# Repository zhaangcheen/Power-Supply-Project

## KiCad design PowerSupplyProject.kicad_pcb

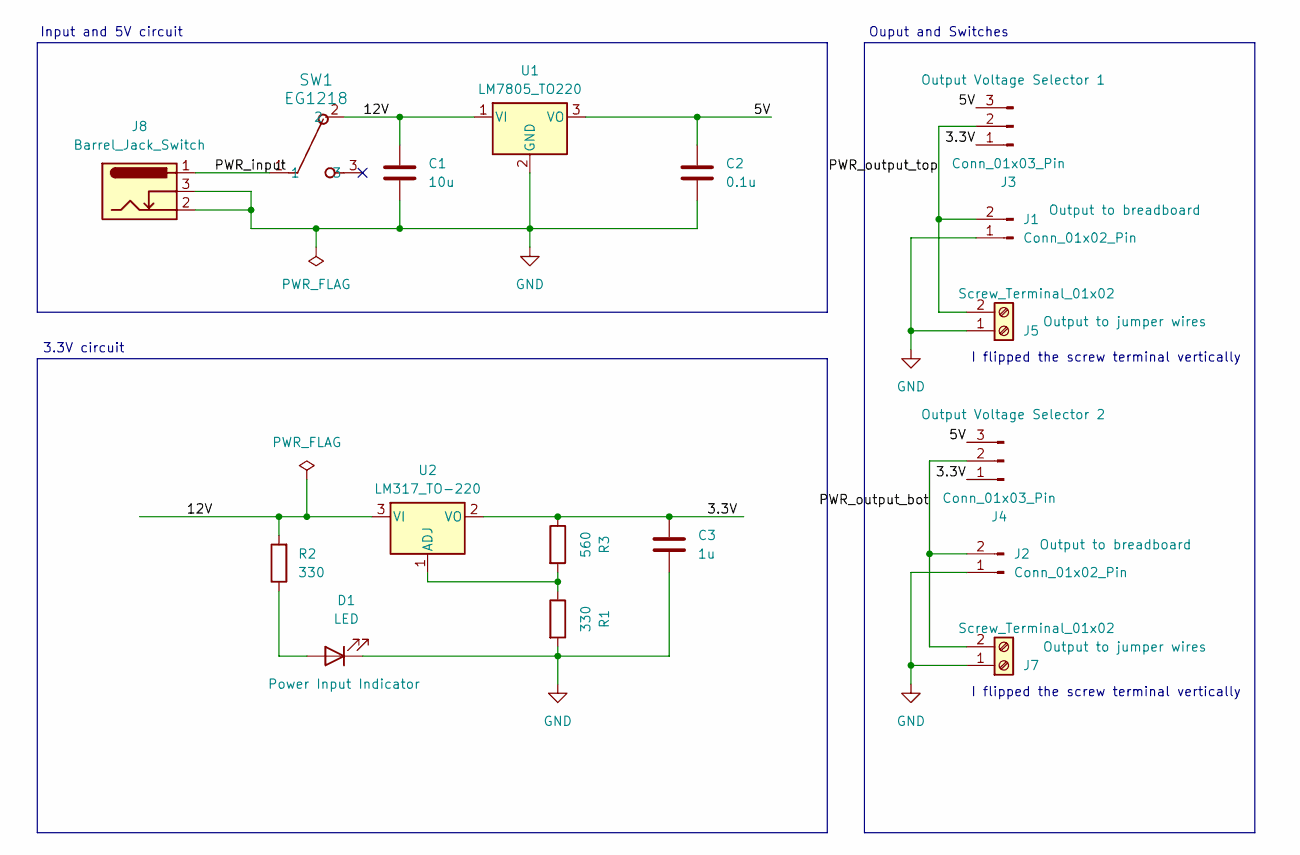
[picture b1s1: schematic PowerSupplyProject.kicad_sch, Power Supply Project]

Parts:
C1: 10u; C_Disc_D3.0mm_W1.6mm_P2.50mm
C2: 0.1u; C_Disc_D3.0mm_W1.6mm_P2.50mm
C3: 1u; C_Disc_D3.0mm_W1.6mm_P2.50mm
D1: LED; LED_D5.0mm
J1, J2: Conn_01x02_Pin; PinHeader_1x02_P2.54mm_Vertical
J3, J4: Conn_01x03_Pin; PinHeader_1x03_P2.54mm_Vertical
J5, J7: Screw_Terminal_01x02; TerminalBlock_bornier-2_P5.08mm
J8: Barrel_Jack_Switch; BarrelJack_Horizontal
R1, R2: 330; R_Axial_DIN0204_L3.6mm_D1.6mm_P7.62mm_Horizontal
R3: 560; R_Axial_DIN0204_L3.6mm_D1.6mm_P7.62mm_Horizontal
SW1: EG1218
U1: LM7805_TO220; TO-220-3_Vertical
U2: LM317_TO-220; TO-220-3_Vertical

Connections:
/3.3V: C3.1, J3.1, J4.1, R3.1, U2.2 (VO)
/5V: C2.1, J3.3, J4.3, U1.3 (VO)
/12V: C1.1, R2.2, SW1.2, U1.1 (VI), U2.3 (VI)
/PWR_input: J8.1, SW1.1
/PWR_output_bot: J2.2, J4.2, J7.2
/PWR_output_top: J1.2, J3.2, J5.2
GND: C1.2, C2.2, C3.2, D1.1 (K), J1.1, J2.1, J5.1, J7.1, J8.2, J8.3, R1.2, U1.2 (GND)
unnamed: D1.2 (A), R2.1
unnamed: R1.1, R3.2, U2.1 (ADJ)

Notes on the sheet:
Input and 5V circuit
Ouput and Switches
3.3V circuit
I flipped the screw terminal vertically

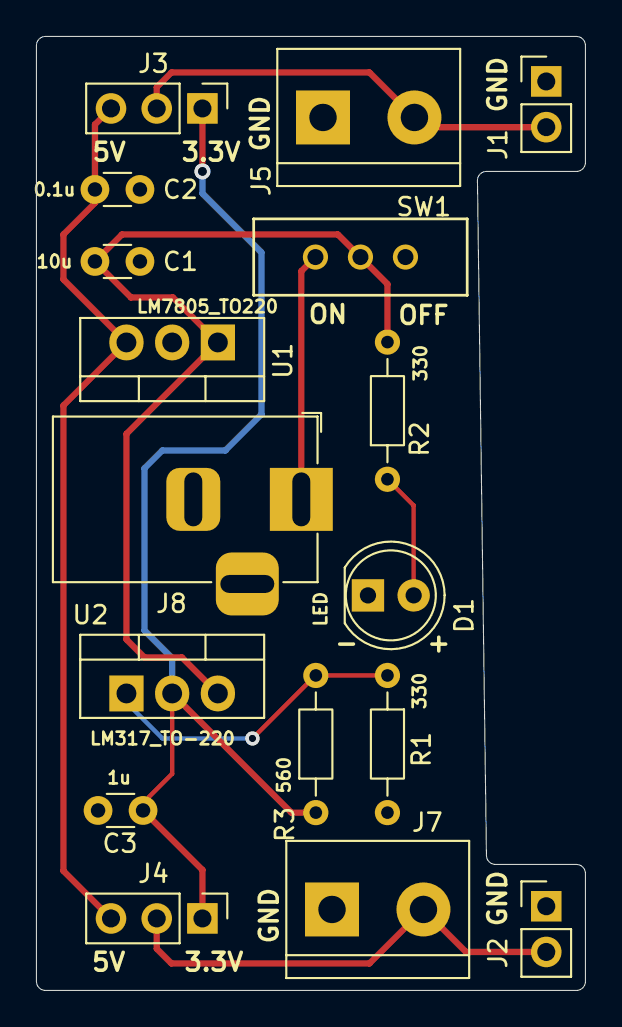
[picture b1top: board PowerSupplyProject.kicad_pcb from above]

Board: 2 copper layers, 30.5 x 53.0 mm, 17 parts (0 on the bottom side), 9 nets.
